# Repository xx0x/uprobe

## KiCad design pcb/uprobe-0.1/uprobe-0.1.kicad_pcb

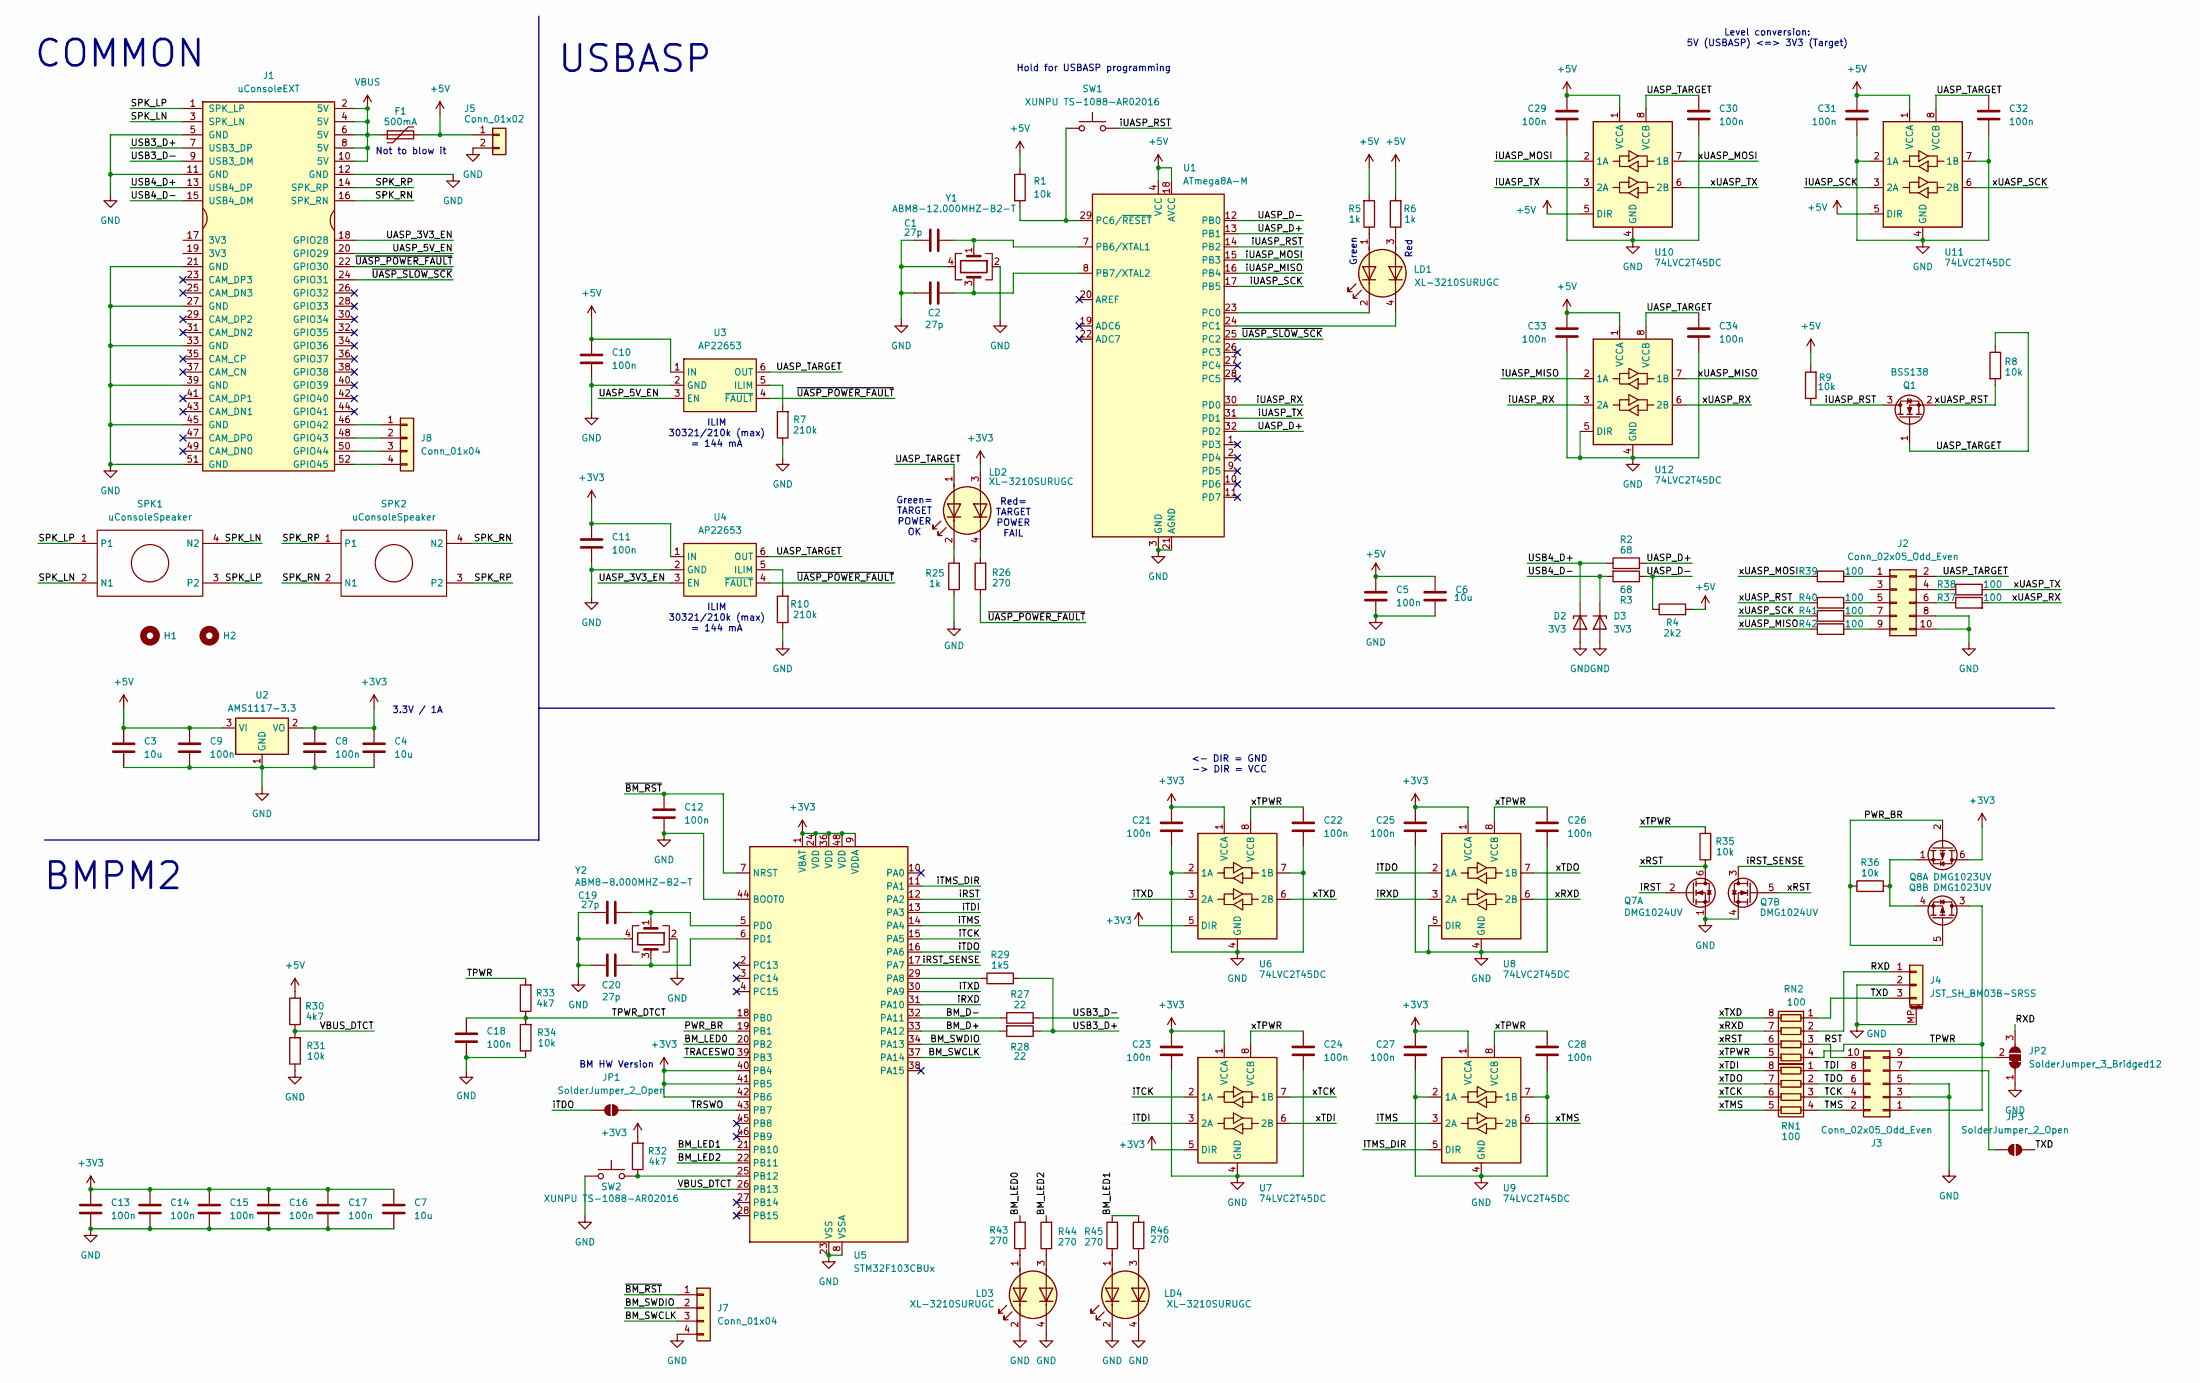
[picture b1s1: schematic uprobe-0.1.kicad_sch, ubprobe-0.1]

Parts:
C1, C2, C19, C20: 27p; C_0603_1608Metric
C3, C4, C6, C7: 10u; C_0805_2012Metric
C5, C8, C9, C10, C11, C12, C13, C14, C15, C16, C17, C18, C21, C22, C23, C24, C25, C26, C27, C28, C29, C30, C31, C32, C33, C34: 100n; C_0603_1608Metric
D2, D3: 3V3; D_SOD-323
F1: 500mA; Fuse_0805_2012Metric
H1, H2: MountingHole; MountingHole_5.3mm_M5
J1: uConsoleEXT; ext
J2: Conn_02x05_Odd_Even; IDC_2x05_SIDE
J3: Conn_02x05_Odd_Even; IDC_2x05_P1.27mm_Horizontal
J4: JST_SH_BM03B-SRSS; JST_SH_BM03B-SRSS-TB_1x03-1MP_P1.00mm_Vertical
J5: Conn_01x02; PinHeader_1x02_P2.54mm_Vertical
J7, J8: Conn_01x04; PinHeader_1x04_P2.54mm_Vertical
JP1, JP3: SolderJumper_2_Open; SolderJumper-2_P1.3mm_Open_TrianglePad1.0x1.5mm
JP2: SolderJumper_3_Bridged12; SolderJumper-3_P2.0mm_Open_TrianglePad1.0x1.5mm
LD1, LD2, LD3, LD4: XL-3210SURUGC
Q1: BSS138; SOT-23
Q7: DMG1024UV; SOT-563
Q8: DMG1023UV; SOT-563
R1, R8, R9, R31, R34, R35, R36: 10k; R_0603_1608Metric
R2, R3: 68; R_0603_1608Metric
R4: 2k2; R_0603_1608Metric
R5, R6, R25: 1k; R_0603_1608Metric
R7, R10: 210k; R_0603_1608Metric
R26, R43, R44, R45, R46: 270; R_0603_1608Metric
R27, R28: 22; R_0603_1608Metric
R29: 1k5; R_0603_1608Metric
R30, R32, R33: 4k7; R_0603_1608Metric
R37, R38, R39, R40, R41, R42: 100; R_0603_1608Metric
RN1, RN2: 100; R_Array_Concave_4x0603
SPK1, SPK2: uConsoleSpeaker; speaker
SW1, SW2: XUNPU TS-1088-AR02016; XUNPU_TS-1088-AR02016
U1: ATmega8A-M; QFN-32-1EP_5x5mm_P0.5mm_EP3.1x3.1mm
U2: AMS1117-3.3; SOT-223-3_TabPin2
U3, U4: AP22653; SOT-23-6
U5: STM32F103CBUx; QFN-48-1EP_7x7mm_P0.5mm_EP5.6x5.6mm
U6, U7, U8, U9, U10, U11, U12: 74LVC2T45DC; VSSOP-8_2.3x2mm_P0.5mm
Y1: ABM8-12.000MHZ-B2-T; Crystal_SMD_Abracon_ABM8G-4Pin_3.2x2.5mm
Y2: ABM8-8.000MHZ-B2-T; Crystal_SMD_Abracon_ABM8G-4Pin_3.2x2.5mm

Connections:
+3V3: C4.1, C7.1, C8.1, C11.1, C13.1, C14.1, C15.1, C16.1, C17.1, C21.1, C23.1, C25.1, C27.1, LD2.3 (A2), Q8.6 (D), R32.2, U2.2 (VO), U4.1 (IN), U5.1 (VBAT), U5.9 (VDDA), U5.24 (VDD), U5.36 (VDD), U5.40 (PB4), U5.41 (PB5), U5.42 (PB6), U5.48 (VDD), U6.1 (VCCA), U6.5 (DIR), U7.1 (VCCA), U7.5 (DIR), U8.1 (VCCA), U9.1 (VCCA)
+5V: C3.1, C5.1, C6.1, C9.1, C10.1, C29.1, C31.1, C33.1, F1.2, J5.1, R1.1, R4.2, R5.2, R6.2, R9.2, R30.2, U1.4 (VCC), U1.6 (VCC), U1.18 (AVCC), U2.3 (VI), U3.1 (IN), U10.1 (VCCA), U10.5 (DIR), U11.1 (VCCA), U11.5 (DIR), U12.1 (VCCA)
/BM_D+: R28.2, U5.33 (PA12)
/BM_D-: R27.1, U5.32 (PA11)
/BM_LED0: R43.2, U5.20 (PB2)
/BM_LED1: R45.2, R46.2, U5.21 (PB10)
/BM_LED2: R44.2, U5.22 (PB11)
/BM_SWCLK: J7.3, U5.37 (PA14)
/BM_SWDIO: J7.2, U5.34 (PA13)
/PWR_BR: Q8.2 (G), Q8.5 (G), R36.1, U5.19 (PB1)
/RST: J3.10, RN2.3 (R3.1)
/RXD: J4.1, JP2.3 (B), RN2.2 (R2.1)
/SPK_LN: J1.3 (SPK_LN), SPK1.2 (N1), SPK1.4 (N2)
/SPK_LP: J1.1 (SPK_LP), SPK1.1, SPK1.3 (P2)
/SPK_RN: J1.16 (SPK_RN), SPK2.2 (N1), SPK2.4 (N2)
/SPK_RP: J1.14 (SPK_RP), SPK2.1, SPK2.3 (P2)
/TCK: J3.4, RN1.3 (R3.1)
/TDI: J3.8, RN1.1 (R1.1)
/TDO: J3.6, RN1.2 (R2.1)
/TMS: J3.2, RN1.4 (R4.1)
/TPWR: J3.1, Q8.3 (D), R33.2, RN2.4 (R4.1)
/TPWR_DTCT: C18.1, R33.1, R34.2, U5.18 (PB0)
/TRACESWO: U5.39 (PB3)
/TRSWO: JP1.2 (B), U5.43 (PB7)
/TXD: J4.3, JP3.2 (B), RN2.1 (R1.1)
/UASP_3V3_EN: J1.18 (GPIO28), U4.3 (EN)
/UASP_5V_EN: J1.20 (GPIO29), U3.3 (EN)
/UASP_D+: R2.2, U1.13 (PB1), U1.32 (PD2)
/UASP_D-: R3.1, R4.1, U1.12 (PB0)
/UASP_TARGET: C30.1, C32.1, C34.1, J2.2, LD2.1 (A1), Q1.1 (G), R8.1, U3.6 (OUT), U4.6 (OUT), U10.8 (VCCB), U11.8 (VCCB), U12.8 (VCCB)
/USB3_D+: J1.7 (USB3_DP), R28.1, R29.2
/USB3_D-: J1.9 (USB3_DM), R27.2
/USB4_D+: D2.1 (K), J1.13 (USB4_DP), R2.1
/USB4_D-: D3.1 (K), J1.15 (USB4_DM), R3.2
/VBUS_DTCT: R30.1, R31.2, U5.26 (PB13)
/iRST: Q7.2 (G), U5.12 (PA2)
/iRST_SENSE: Q7.3 (D), U5.17 (PA7)
/iRXD: U5.31 (PA10), U8.3 (2A)
/iTCK: U5.15 (PA5), U7.2 (1A)
/iTDI: U5.13 (PA3), U7.3 (2A)
/iTDO: JP1.1 (A), U5.16 (PA6), U8.2 (1A)
/iTMS: U5.14 (PA4), U9.3 (2A)
/iTMS_DIR: U5.11 (PA1), U9.5 (DIR)
/iTXD: U5.30 (PA9), U6.3 (2A)
/iUASP_MISO: U1.16 (PB4), U12.2 (1A)
/iUASP_MOSI: U1.15 (PB3), U10.2 (1A)
/iUASP_RST: Q1.3 (D), R9.1, SW1.2, U1.14 (PB2)
/iUASP_RX: U1.30 (PD0), U12.3 (2A)
/iUASP_SCK: U1.17 (PB5), U11.3 (2A)
/iUASP_TX: U1.31 (PD1), U10.3 (2A)
/xRST: Q7.5 (G), Q7.6 (D), R35.1, RN2.6 (R3.2)
/xRXD: RN2.7 (R2.2), U8.6 (2B)
/xTCK: RN1.6 (R3.2), U7.7 (1B)
/xTDI: RN1.8 (R1.2), U7.6 (2B)
/xTDO: RN1.7 (R2.2), U8.7 (1B)
/xTMS: RN1.5 (R4.2), U9.6 (2B)
/xTPWR: C22.1, C24.1, C26.1, C28.1, R35.2, RN2.5 (R4.2), U6.8 (VCCB), U7.8 (VCCB), U8.8 (VCCB), U9.8 (VCCB)
/xTXD: RN2.8 (R1.2), U6.6 (2B)
/xUASP_MISO: R42.1, U12.7 (1B)
/xUASP_MOSI: R39.1, U10.7 (1B)
/xUASP_RST: Q1.2 (S), R8.2, R40.1
/xUASP_RX: R37.2, U12.6 (2B)
/xUASP_SCK: R41.1, U11.6 (2B)
/xUASP_TX: R38.2, U10.6 (2B)
/~BM_RST: C12.1, J7.1, U5.7 (NRST)
/~UASP_POWER_FAULT: J1.22 (GPIO30), R26.1, U3.4 (~FAULT), U4.4 (~FAULT)
/~UASP_SLOW_SCK: J1.24 (GPIO31), U1.25 (PC2)
GND: C1.1, C2.1, C3.2, C4.2, C5.2, C6.2, C7.2, C8.2, C9.2, C10.2, C11.2, C12.2, C13.2, C14.2, C15.2, C16.2, C17.2, C18.2, C19.1, C20.1, C21.2, C22.2, C23.2, C24.2, C25.2, C26.2, C27.2, C28.2, C29.2, C30.2, C31.2, C32.2, C33.2, C34.2, D2.2 (A), D3.2 (A), J1.5 (GND), J1.11 (GND), J1.12 (GND), J1.21 (GND), J1.27 (GND), J1.33 (GND), J1.39 (GND), J1.45 (GND), J1.51 (GND), J2.8, J2.10, J3.3, J3.5, J4.2, J4.MP (MountPin), J5.2, J7.4, JP2.1 (A), LD3.2 (K1), LD3.4 (K2), LD4.2 (K1), LD4.4 (K2), Q7.1 (S), Q7.4 (S), R7.1, R10.1, R25.1, R31.1, R34.1, SW2.1, U1.3 (GND), U1.5 (GND), U1.21 (AGND), U1.33 (GND), U2.1 (GND), U3.2 (GND), U4.2 (GND), U5.8 (VSSA), U5.23 (VSS), U5.35 (VSS), U5.44 (BOOT0), U5.47 (VSS), U5.49 (VSS), U6.2 (1A), U6.4 (GND), U6.7 (1B), U7.4 (GND), U8.4 (GND), U8.5 (DIR), U9.2 (1A), U9.4 (GND), U9.7 (1B), U10.4 (GND), U11.2 (1A), U11.4 (GND), U11.7 (1B), U12.4 (GND), U12.5 (DIR), Y1.2, Y1.4, Y2.2, Y2.4
unnamed: J1.46 (GPIO42), J8.1
unnamed: J1.48 (GPIO43), J8.2
unnamed: J1.50 (GPIO44), J8.3
unnamed: J1.52 (GPIO45), J8.4
unnamed: J2.1, R39.2
unnamed: J2.4, R38.1
unnamed: J2.5, R40.2
unnamed: J2.6, R37.1
unnamed: J2.7, R41.2
unnamed: J2.9, R42.2
unnamed: J3.7, JP3.1 (A)
unnamed: J3.9, JP2.2 (C)
unnamed: LD1.1 (A1), R5.1
unnamed: LD1.3 (A2), R6.1
unnamed: LD1.2 (K1), U1.23 (PC0)
unnamed: LD1.4 (K2), U1.24 (PC1)
unnamed: LD2.2 (K1), R25.2
unnamed: LD2.4 (K2), R26.2
unnamed: LD3.1 (A1), R43.1
unnamed: LD3.3 (A2), R44.1
unnamed: LD4.1 (A1), R45.1
unnamed: LD4.3 (A2), R46.1
unnamed: Q8.1 (S), Q8.4 (S), R36.2
unnamed: C1.2, U1.7 (PB6/XTAL1), Y1.1
unnamed: C2.2, U1.8 (PB7/XTAL2), Y1.3
unnamed: R1.2, SW1.1, U1.29 (PC6/~RESET)
unnamed: R7.2, U3.5 (ILIM)
unnamed: R10.2, U4.5 (ILIM)
unnamed: R29.1, U5.29 (PA8)
unnamed: R32.1, SW2.2, U5.25 (PB12)
unnamed: C19.2, U5.5 (PD0), Y2.1
unnamed: C20.2, U5.6 (PD1), Y2.3
VBUS: F1.1, J1.2 (5V), J1.4 (5V), J1.6 (5V), J1.8 (5V), J1.10 (5V)

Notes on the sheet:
<- DIR = GND -> DIR = VCC
Not to blow it
Red= TARGET POWER FAIL
3.3V / 1A
BMPM2
USBASP
COMMON
BM HW Version
Red
Hold for USBASP programming
Green
ILIM 30321/210k (max) = 144 mA
Level conversion: 5V (USBASP) <=> 3V3 (Target)
Green= TARGET POWER OK

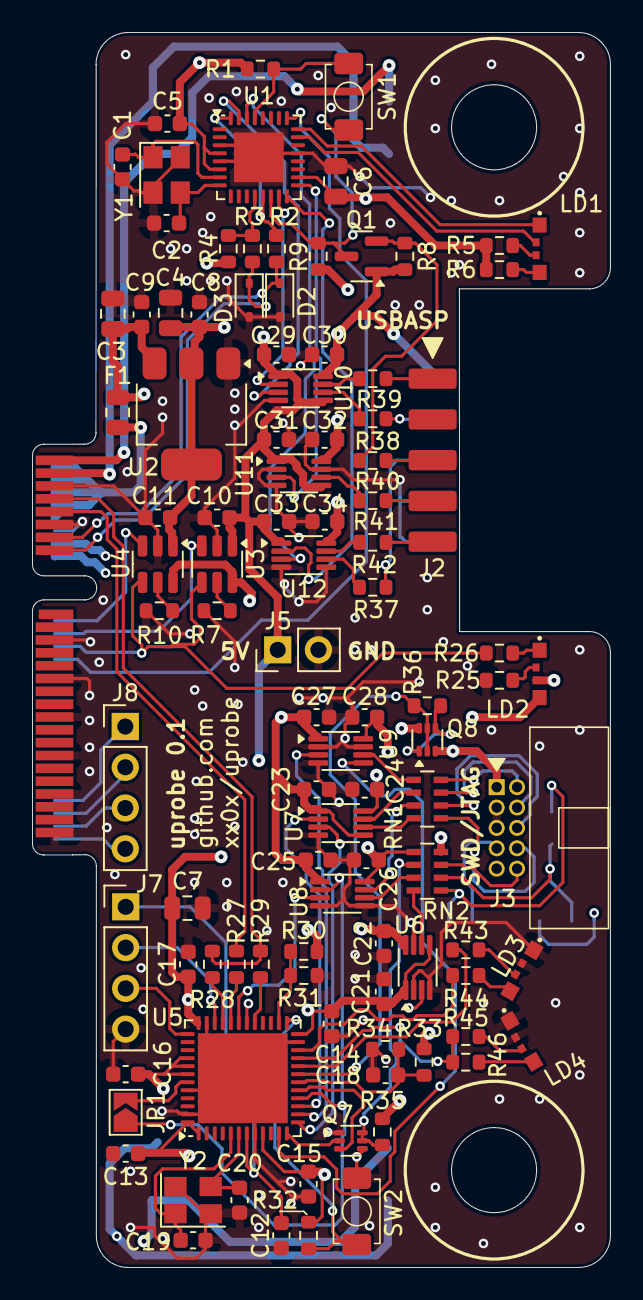
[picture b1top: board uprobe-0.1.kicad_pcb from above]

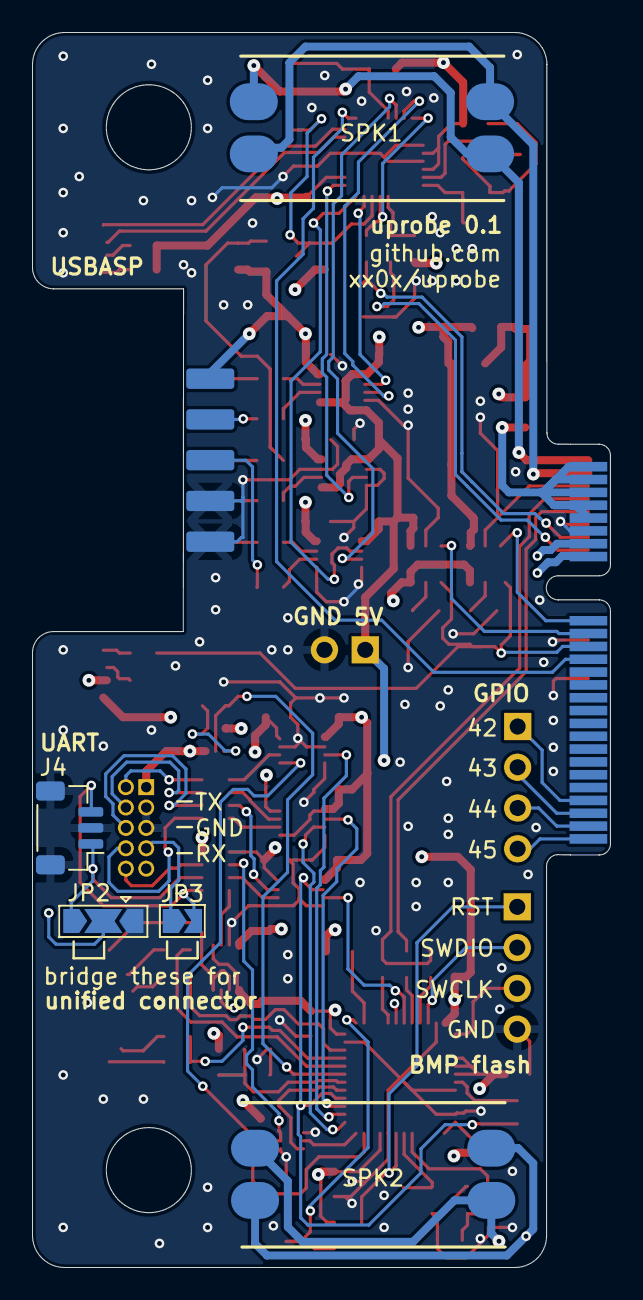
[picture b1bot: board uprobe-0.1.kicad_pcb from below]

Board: 4 copper layers, 36.0 x 77.0 mm, 108 parts (5 on the bottom side), 100 nets.

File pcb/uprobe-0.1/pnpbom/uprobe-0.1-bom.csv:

Designator,Footprint,Quantity,Comment,Supplier and ref
"C23,C24,C9,C27,C21,C11,C25,C33,C22,C34,C5,C10,C30,C18,C16,C17,C31,C32,C13,C29,C15,C12,C28,C8,C26,C14",C_0603_1608Metric,26,100n,
"U7,U9,U6,U10,U11,U12,U8",VSSOP-8_2.3x2mm_P0.5mm,7,74LVC2T45DC,
"C4,C6,C7,C3",C_0805_2012Metric,4,10u,
"RN2,RN1",R_Array_Concave_4x0603,2,100,
"U3,U4",SOT-23-6,2,AP22653,
"R45,R46,R26,R43,R44",R_0603_1608Metric,5,270,
"LD2,LD4,LD3,LD1",XL-3210SURUGC,4,XL-3210SURUGC,
"R32,R33,R30",R_0603_1608Metric,3,4k7,
"R9,R31,R35,R34,R1,R36,R8",R_0603_1608Metric,7,10k,
R4,R_0603_1608Metric,1,2k2,
"R41,R39,R42,R38,R37,R40",R_0603_1608Metric,6,100,
F1,Fuse_0805_2012Metric,1,500mA,
Y2,Crystal_SMD_Abracon_ABM8G-4Pin_3.2x2.5mm,1,ABM8-8.000MHZ-B2-T,
"C19,C1,C2,C20",C_0603_1608Metric,4,27p,
"R6,R25,R5",R_0603_1608Metric,3,1k,
Y1,Crystal_SMD_Abracon_ABM8G-4Pin_3.2x2.5mm,1,ABM8-12.000MHZ-B2-T,
"R2,R3",R_0603_1608Metric,2,68,
"R7,R10",R_0603_1608Metric,2,210k,
U5,QFN-48-1EP_7x7mm_P0.5mm_EP5.6x5.6mm,1,STM32F103CBUx,
"SW1,SW2",XUNPU_TS-1088-AR02016,2,XUNPU TS-1088-AR02016,
R29,R_0603_1608Metric,1,1k5,
Q8,SOT-563,1,DMG1023UV,
Q7,SOT-563,1,DMG1024UV,
"D3,D2",D_SOD-323,2,3V3,
U1,QFN-32-1EP_5x5mm_P0.5mm_EP3.1x3.1mm,1,ATmega8A-M,
"R28,R27",R_0603_1608Metric,2,22,
Q1,SOT-23,1,BSS138,
U2,SOT-223-3_TabPin2,1,AMS1117-3.3,

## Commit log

2025-03-15 basics: board outline, connector, speakers, holes
2025-03-16 working on usbasp section
2025-03-16 add level shifter sim, schema in prog
2025-03-17 add bmp schematics
2025-03-18 update usbasp schema
2025-03-18 layout update
2025-03-19 routing
2025-03-21 routing cleanup
2025-03-21 silkscreen
2025-03-21 additional gpio
2025-03-21 add gerber, pnp and bom
2025-03-31 update firmwares readme and gitignore
2025-04-18 schematic notes and power script for usbasp

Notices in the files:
pcb/uprobe-0.1/uprobe-0.1.kicad_pcb:
License: CC-BY-SA 4.0
